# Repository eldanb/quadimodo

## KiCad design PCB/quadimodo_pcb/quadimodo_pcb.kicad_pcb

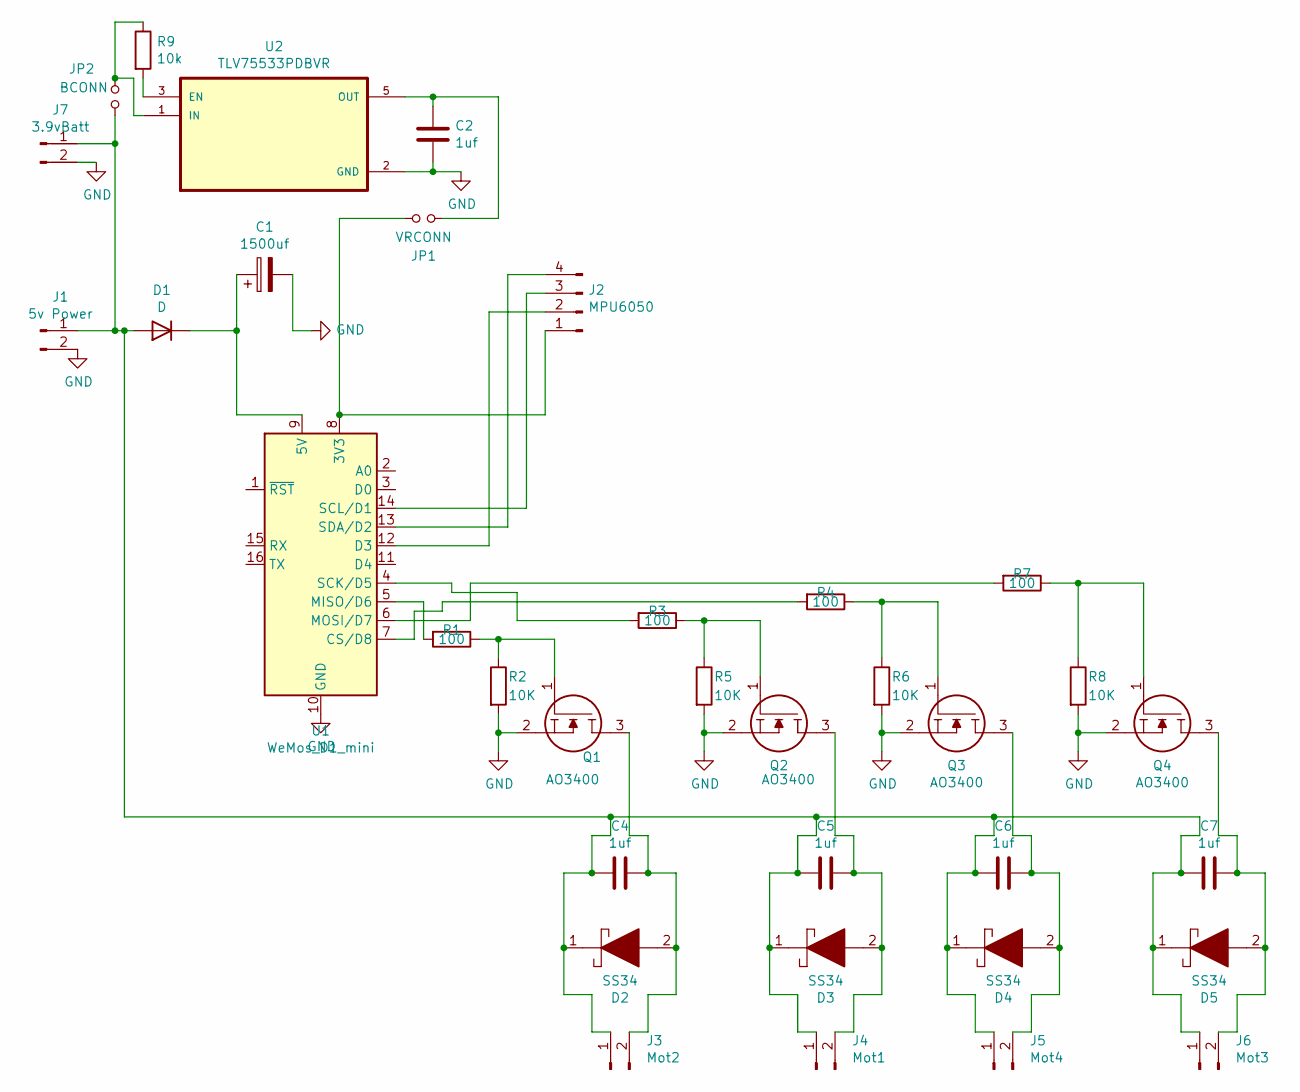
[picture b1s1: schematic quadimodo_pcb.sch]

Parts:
C1: 1500uf; CP_Radial_D10.0mm_P3.50mm
C2, C4, C5, C6, C7: 1uf; C_0805_2012Metric; LCSC C28323
D1: D; D_A-405_P10.16mm_Horizontal
D2, D3, D4, D5: SS34; DIOM5026X262N; Manufacturer_Part_Number SS34; LCSC C8678
J1: 5v Power; PinHeader_1x02_P2.54mm_Vertical
J2: MPU6050; PinHeader_1x04_P2.54mm_Vertical
J3: Mot2; PinHeader_1x02_P2.54mm_Vertical
J4: Mot1; PinHeader_1x02_P2.54mm_Vertical
J5: Mot4; PinHeader_1x02_P2.54mm_Vertical
J6: Mot3; PinHeader_1x02_P2.54mm_Vertical
J7: 3.9vBatt; PinHeader_1x02_P2.54mm_Vertical
JP1: VRCONN; SolderJumper-2_P1.3mm_Open_RoundedPad1.0x1.5mm
JP2: BCONN; SolderJumper-2_P1.3mm_Open_RoundedPad1.0x1.5mm
Q1, Q2, Q3, Q4: AO3400; SOT95P280X125-3N; Manufacturer_Part_Number SQ2310ES-T1_GE3; Mouser Part Number 78-SQ2310ES-T1_GE3
R1, R3, R4, R7: 100; R_0805_2012Metric
R2, R5, R6, R8: 10K; R_0805_2012Metric
R9: 10k; R_0805_2012Metric
U1: WeMos_D1_mini; WEMOS_D1_mini_light
U2: TLV75533PDBVR; SOT95P280X145-5N; LCSC C404027

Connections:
GND: C1.2, C2.2, J1.2, J7.2, Q1.2, Q2.2, Q3.2, Q4.2, R2.2, R5.2, R6.2, R8.2, U1.10 (GND), U2.2 (GND)
unnamed: C1.1, D1.1 (K), U1.9 (5V)
unnamed: C2.1, JP1.2, U2.5 (OUT)
unnamed: C4.1, D2.2, J3.2, Q1.3
unnamed: C4.2, C5.2, C6.2, C7.2, D1.2 (A), D2.1, D3.1, D4.1, D5.1, J1.1, J3.1, J4.1, J5.1, J6.1, J7.1, JP2.1
unnamed: C5.1, D3.2, J4.2, Q2.3
unnamed: C6.1, D4.2, J5.2, Q3.3
unnamed: C7.1, D5.2, J6.2, Q4.3
unnamed: J2.1, JP1.1, U1.8 (3V3)
unnamed: J2.2, U1.12 (D3)
unnamed: J2.3, U1.14 (SCL/D1)
unnamed: J2.4, U1.13 (SDA/D2)
unnamed: JP2.2, R9.1, U2.1 (IN)
unnamed: Q1.1, R1.1, R2.1
unnamed: Q2.1, R3.1, R5.1
unnamed: Q3.1, R4.1, R6.1
unnamed: Q4.1, R7.1, R8.1
unnamed: R1.2, U1.5 (MISO/D6)
unnamed: R3.2, U1.4 (SCK/D5)
unnamed: R4.2, U1.7 (CS/D8)
unnamed: R7.2, U1.6 (MOSI/D7)
unnamed: R9.2, U2.3 (EN)

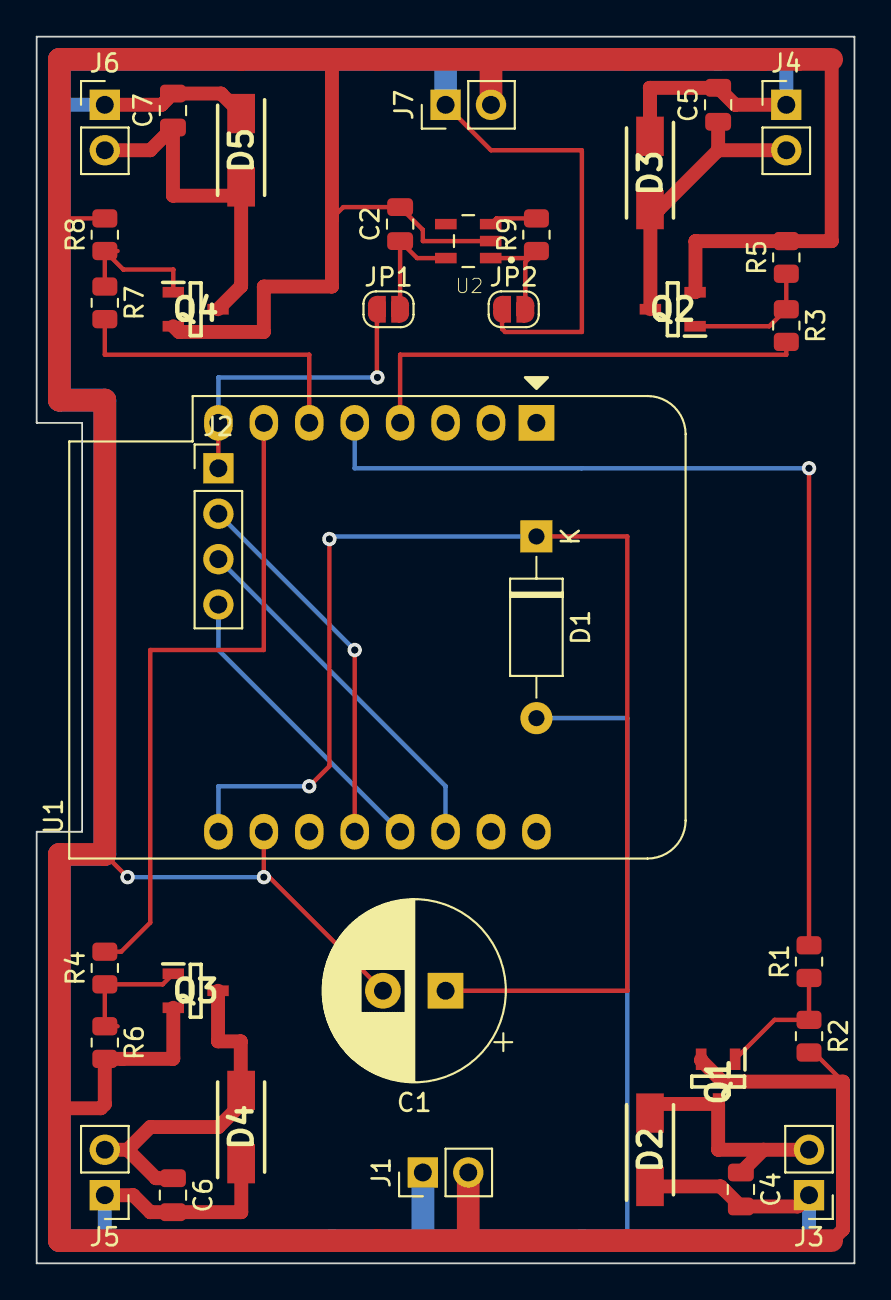
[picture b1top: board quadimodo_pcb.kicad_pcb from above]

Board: 2 copper layers, 45.7 x 68.6 mm, 35 parts (0 on the bottom side), 22 nets.

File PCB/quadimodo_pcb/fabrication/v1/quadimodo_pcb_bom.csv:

Comment,Designator,Footprint,LCSC
"1500uf","C1,C3","Capacitor_THT:CP_Radial_D10.0mm_P3.50mm",""
"1uf","C2,C4,C5,C6,C7","Capacitor_SMD:C_0805_2012Metric","C28323"
"D","D1","Diode_THT:D_A-405_P10.16mm_Horizontal",""
"5v Power","J1","Connector_PinHeader_2.54mm:PinHeader_1x02_P2.54mm_Vertical",""
"MPU6050","J2","Connector_PinHeader_2.54mm:PinHeader_1x04_P2.54mm_Vertical",""
"Mot2","J3","Connector_PinHeader_2.54mm:PinHeader_1x02_P2.54mm_Vertical",""
"Mot1","J4","Connector_PinHeader_2.54mm:PinHeader_1x02_P2.54mm_Vertical",""
"Mot4","J5","Connector_PinHeader_2.54mm:PinHeader_1x02_P2.54mm_Vertical",""
"Mot3","J6","Connector_PinHeader_2.54mm:PinHeader_1x02_P2.54mm_Vertical",""
"3.9vBatt","J7","Connector_PinHeader_2.54mm:PinHeader_1x02_P2.54mm_Vertical",""
"VRCONN","JP1","Jumper:SolderJumper-2_P1.3mm_Open_RoundedPad1.0x1.5mm",""
"BCONN","JP2","Jumper:SolderJumper-2_P1.3mm_Open_RoundedPad1.0x1.5mm",""
"AO3400","Q1,Q2,Q3,Q4","quadimodo_imported_footprints:SOT95P280X125-3N"," C347475"
"10K","R2,R5,R6,R8","Resistor_SMD:R_0805_2012Metric",""
"100","R1,R3,R4,R7","Resistor_SMD:R_0805_2012Metric",""
"10k","R9","Resistor_SMD:R_0805_2012Metric",""
"WeMos_D1_mini","U1","Module:WEMOS_D1_mini_light",""
"TLV75533PDBVR","U2","quadimodo_imported_footprints:SOT95P280X145-5N","C404027"
